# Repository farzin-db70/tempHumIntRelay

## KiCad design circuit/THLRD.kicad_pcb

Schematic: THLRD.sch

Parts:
C1, C4, C5, C6, C7: 100nf; C_0805_2012Metric_Pad1.15x1.40mm_HandSolder
C2, C3: 10uf-10v-tantal; CP_EIA-3216-18_Kemet-A
D1, D2: LL4148; D_MiniMELF
J1: Phonix-Green2; TerminalBlock-2-5.08mm
J2: HDR-40PIN-100mil; MODULE_ESP32-DEVKITC-32D
J3: XH-2Pin-100mil-Right; JST_PH_S2B-PH-K_1x02_P2.00mm_Horizontal
J4: Terminal 3pin; TerminalBlock-3-5.08mm
K1, K2: NRP05-A05D; NRP05-AXX
Q1, Q2: MMBT3904; SOT-23
R1: MLG5516; R_LDR_4.9x4.2mm_P2.54mm_Vertical
R2: 5K; R_0805_2012Metric_Pad1.15x1.40mm_HandSolder
R3, R4, R5: 1K; R_0805_2012Metric_Pad1.15x1.40mm_HandSolder
R6, R7: 10K; R_0805_2012Metric_Pad1.15x1.40mm_HandSolder
RV1: POT-10K; Potentiometer_Bourns_3296W_Vertical
U1: LM1117-3.3; SOT-223-3_TabPin2
U2: LM358; SO-8_5.3x6.2mm_P1.27mm
U3: DHT11; Aosong_DHT11_5.5x12.0_P2.54mm
U4: SHT1x

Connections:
+3V3: C3.1, C5.2, C6.2, R1.1, U1.2, U3.1 (VCC), U4.4 (VDD)
+5V: C1.2, C2.1, C4.1, D1.1 (K), D2.1 (K), J1.2, J2.19, K1.1, K2.2, U1.3, U2.8
/CLK: J2.38
/CMD: J2.18
/EN: J2.2
/IO0: J2.33
/IO2: J2.34
/IO5: J2.29
/IO12: J2.13, R1.2, R2.1
/IO13: J2.15
/IO14: J2.12, U3.2 (IO)
/IO15: C7.1, J2.35, RV1.2, U2.1
/IO17: J2.30
/IO18: J2.28
/IO19: J2.27
/IO21: J2.25, R5.2
/IO22: J2.22
/IO23: J2.21
/IO25: J2.9
/IO26: J2.10
/IO27: J2.11
/IO32: J2.7
/IO33: J2.8
/IO34: J2.5, R4.2
/IO35: J2.6
/RX0: J2.24
/SCL: J2.31, U4.3 (SCK)
/SD2: J2.16
/SD3: J2.17
/SDA: J2.32, U4.2 (DATA)
/SDI: J2.36
/SDO: J2.37
/TX0: J2.23
/VN: J2.4
/VP: J2.3
GND: C1.1, C2.2, C3.2, C4.2, C5.1, C6.1, C7.2, J1.1, J2.14, J2.26, J3.1, Q1.2, Q2.2, R2.2, R6.2, R7.2, U1.1, U2.2, U2.4, U3.4 (GND), U4.1 (GND)
unnamed: D1.2 (A), K1.2, Q1.3
unnamed: D2.2 (A), K2.1, Q2.3
unnamed: J3.2, R3.1
unnamed: J4.1, K1.4
unnamed: J4.2, K1.3, K2.4
unnamed: J4.3, K2.3
unnamed: Q1.1, R4.1, R6.1
unnamed: Q2.1, R5.1, R7.1
unnamed: R3.2, RV1.3, U2.3

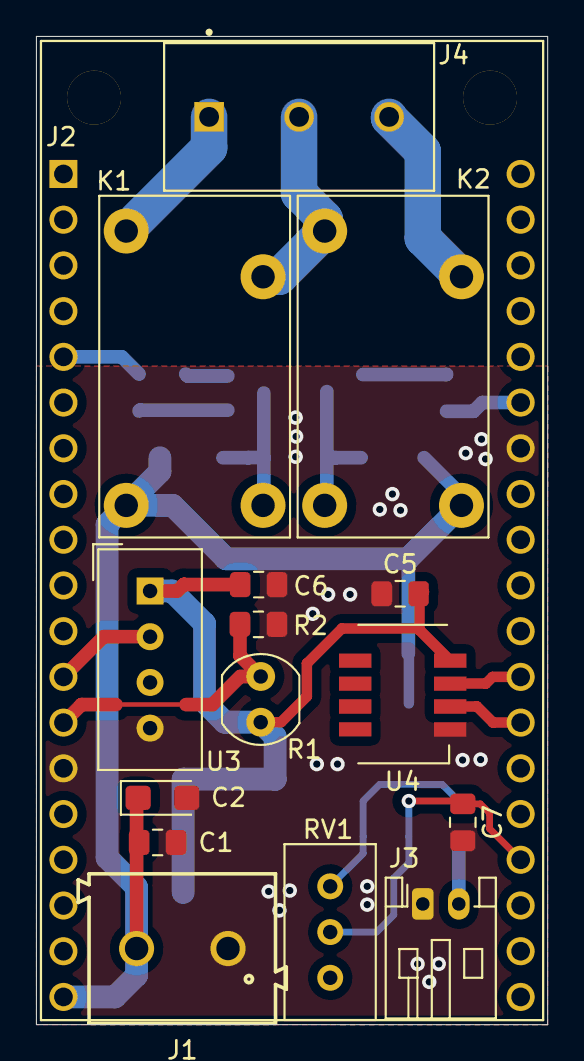
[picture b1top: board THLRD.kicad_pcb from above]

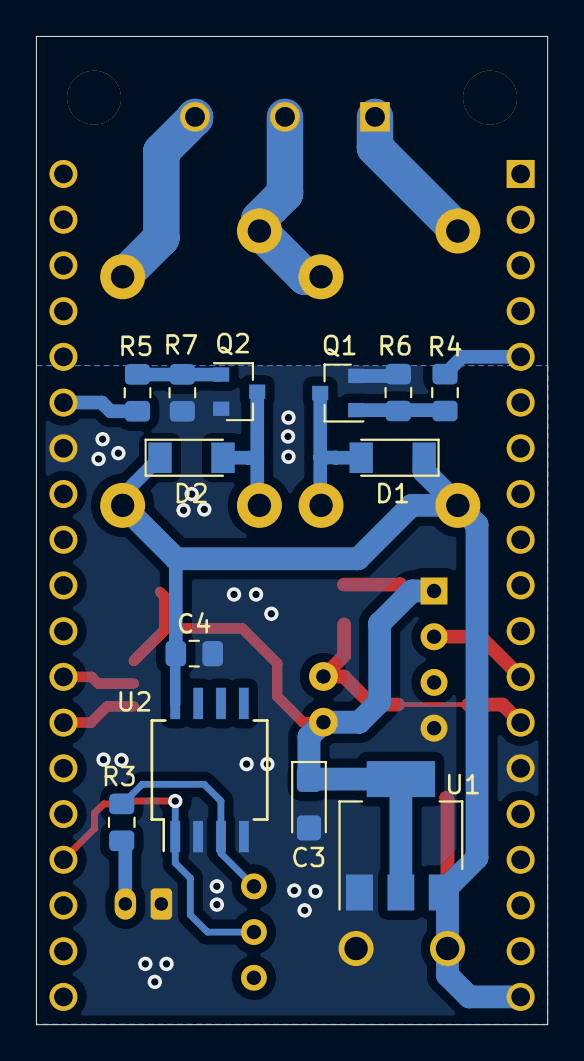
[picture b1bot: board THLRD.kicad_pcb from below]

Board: 2 copper layers, 28.4 x 54.9 mm, 29 parts (13 on the bottom side), 19 nets.

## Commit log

2021-10-21 first commit : add circuit and PCB
